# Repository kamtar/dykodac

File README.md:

# dykodac
Prototype of USB DAC using <b>CS4398</b>, AD712J and TPA6120A2 as a headphone amplifier. MCU - ATSAMD51<br>
Designed with 15V/1A transformer in mind, simple and linear power supply.

[Schematics in pdf](./schematics/DykoDAC.pdf)

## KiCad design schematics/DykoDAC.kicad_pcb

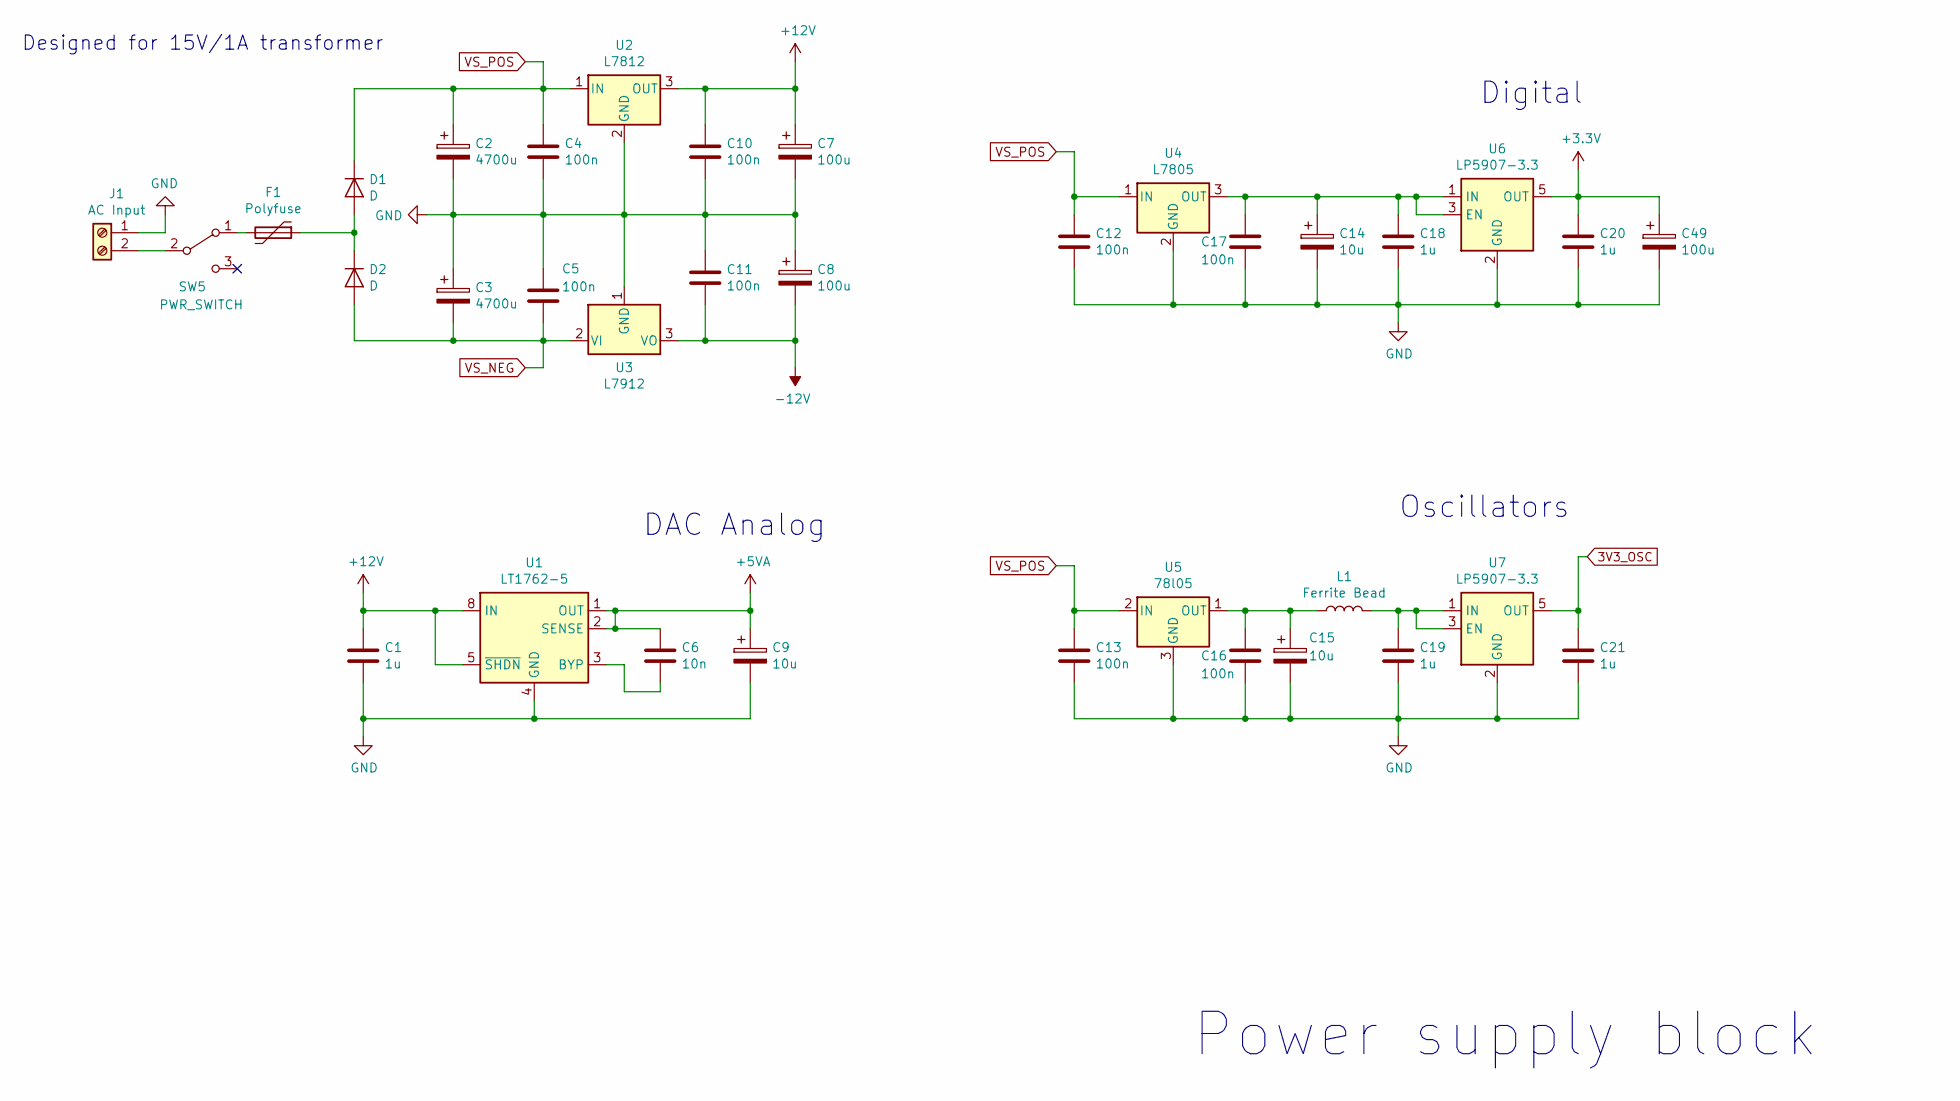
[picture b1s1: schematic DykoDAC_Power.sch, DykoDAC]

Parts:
C1, C18, C19, C20, C21: 1u; C_0603
C2, C3: 4700u; CP_Radial_D16.0mm_P7.50mm_Hor
C4, C5, C10, C11, C12, C13, C16, C17: 100n; C_0603
C6: 10n; C_0603
C7: 100u; CP_EIA-7343-31_Kemet-D; Part TAJD107K016SNJ
C8, C49: 100u; CP_EIA-7343-31_Kemet-D
C9: 10u; CP_EIA-3216-18_Kemet-A; Part T491A106K016AT
C14, C15: 10u; CP_EIA-3216-18_Kemet-A
D1, D2: D; D_SMB
F1: Polyfuse; UNIFuse_SMD2920
J1: AC Input; TerminalBlock_Altech_AK300-2_P5.00mm
L1: Ferrite Bead; C_0603
SW5: PWR_SWITCH; SW_Push_1P2T_Vertical_E-Switch_800UDP8P1A1M6
U1: LT1762-5; MSOP-8_3x3mm_Pitch0.65mm
U2: L7812; TO-263-2
U3: L7912; TO-263-2
U4: L7805; TO-263-2
U5: 78l05; SOT-23
U6, U7: LP5907-3.3; SOT-23-5

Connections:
3V3_OSC: C21.1, U7.5 (OUT); also elsewhere on the board
+5VA: C6.1, C9.1, U1.1 (OUT), U1.2 (SENSE); also elsewhere on the board
+12V: C1.1, C7.1, C10.1, U1.5 (~SHDN), U1.8 (IN), U2.3 (OUT); also elsewhere on the board
-12V: C8.2, C11.2, U3.3 (VO); also elsewhere on the board
GND: C1.2, C2.2, C3.1, C4.2, C5.1, C7.2, C8.1, C9.2, C10.2, C11.1, C12.2, C13.2, C14.2, C15.2, C16.2, C17.2, C18.2, C19.2, C20.2, C21.2, C49.2, J1.1, U1.4 (GND), U2.2 (GND), U3.1 (GND), U4.2 (GND), U5.3 (GND), U6.2 (GND), U7.2 (GND); also elsewhere on the board
unnamed: C6.2, U1.3 (BYP)
unnamed: C14.1, C17.1, C18.1, U4.3 (OUT), U6.1 (IN), U6.3 (EN)
unnamed: C15.1, C16.1, L1.1, U5.1 (OUT)
unnamed: C19.1, L1.2, U7.1 (IN), U7.3 (EN)
unnamed: D1.2 (A), D2.1 (K), F1.1
unnamed: F1.2, SW5.1 (A)
unnamed: J1.2, SW5.2 (B)
VS_NEG: C3.2, C5.2, D2.2 (A), U3.2 (VI)
VS_POS: C2.1, C4.1, C12.1, C13.1, D1.1 (K), U2.1 (IN), U4.1 (IN), U5.2 (IN)

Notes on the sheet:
Digital
DAC Analog
Power supply block
Oscillators
Designed for 15V/1A transformer

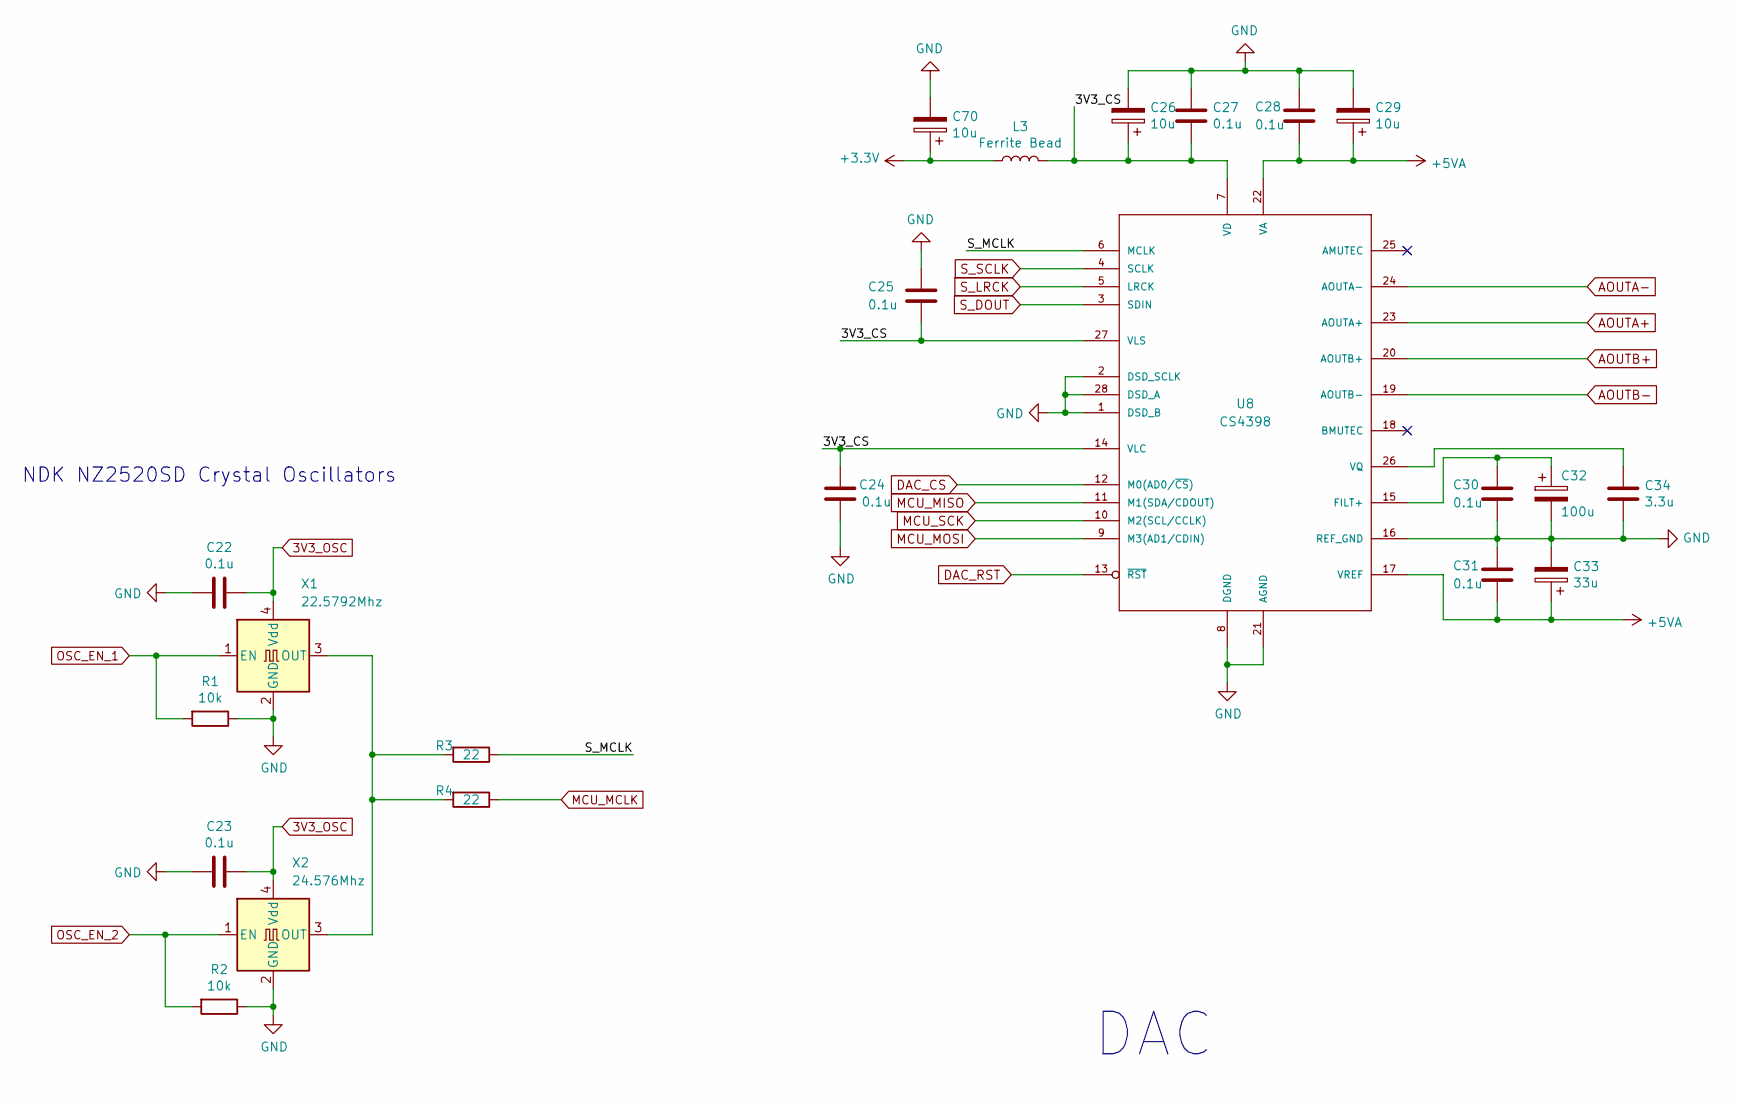
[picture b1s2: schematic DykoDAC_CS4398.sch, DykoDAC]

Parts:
C22, C23, C24, C25, C27, C28, C30, C31: 0.1u; C_0603
C26, C29, C70: 10u; CP_EIA-3216-18_Kemet-A
C32: 100u; CP_EIA-7343-31_Kemet-D; Part TAJD107K016SNJ
C33: 33u; CP_EIA-3216-18_Kemet-A
C34: 3.3u; C_0805
L3: Ferrite Bead; C_0603_1608Metric
R1, R2: 10k; R_0603
R3, R4: 22; R_0603
U8: CS4398; TSSOP-28_4.4x9.7mm_Pitch0.65mm
X1: 22.5792Mhz; Oscillator_SMD_SeikoEpson_SG210-4pin_2.5x2.0mm_HandSoldering; Part NDK NZ2520SD
X2: 24.576Mhz; Oscillator_SMD_SeikoEpson_SG210-4pin_2.5x2.0mm_HandSoldering; Part NDK NZ2520SD

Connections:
3V3_OSC: C22.1, C23.1, X1.4 (Vdd), X2.4 (Vdd); also elsewhere on the board
+5VA: C28.2, C29.1, C31.2, C33.1, U8.17 (VREF), U8.22 (VA); also elsewhere on the board
/DykoDAC_CS4398/3V3_CS: C24.1, C25.1, C26.1, C27.1, L3.2, U8.7 (VD), U8.14 (VLC), U8.27 (VLS)
/DykoDAC_CS4398/S_MCLK: R3.1, U8.6 (MCLK)
AOUTA+: U8.23 (AOUTA+); also elsewhere on the board
AOUTA-: U8.24 (AOUTA-); also elsewhere on the board
AOUTB+: U8.20 (AOUTB+); also elsewhere on the board
AOUTB-: U8.19 (AOUTB-); also elsewhere on the board
DAC_CS: U8.12 (M0(AD0/~CS~)); also elsewhere on the board
DAC_RST: U8.13 (~RST); also elsewhere on the board
GND: C22.2, C23.2, C24.2, C25.2, C26.2, C27.2, C28.1, C29.2, C30.2, C31.1, C32.2, C33.2, C34.2, C70.2, R1.1, R2.1, U8.1 (DSD_B), U8.2 (DSD_SCLK), U8.8 (DGND), U8.16 (REF_GND), U8.21 (AGND), U8.28 (DSD_A), X1.2 (GND), X2.2 (GND); also elsewhere on the board
MCU_MCLK: R4.1; also elsewhere on the board
MCU_MISO: U8.11 (M1(SDA/CDOUT)); also elsewhere on the board
MCU_MOSI: U8.9 (M3(AD1/CDIN)); also elsewhere on the board
MCU_SCK: U8.10 (M2(SCL/CCLK)); also elsewhere on the board
unnamed: C30.1, C32.1, U8.15 (FILT+)
unnamed: C34.1, U8.26 (VQ)
unnamed: R3.2, R4.2, X1.3 (OUT), X2.3 (OUT)
OSC_EN_1: R1.2, X1.1 (EN); also elsewhere on the board
OSC_EN_2: R2.2, X2.1 (EN); also elsewhere on the board
S_DOUT: U8.3 (SDIN); also elsewhere on the board
S_LRCK: U8.5 (LRCK); also elsewhere on the board
S_SCLK: U8.4 (SCLK); also elsewhere on the board

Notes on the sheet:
DAC
NDK NZ2520SD Crystal Oscillators

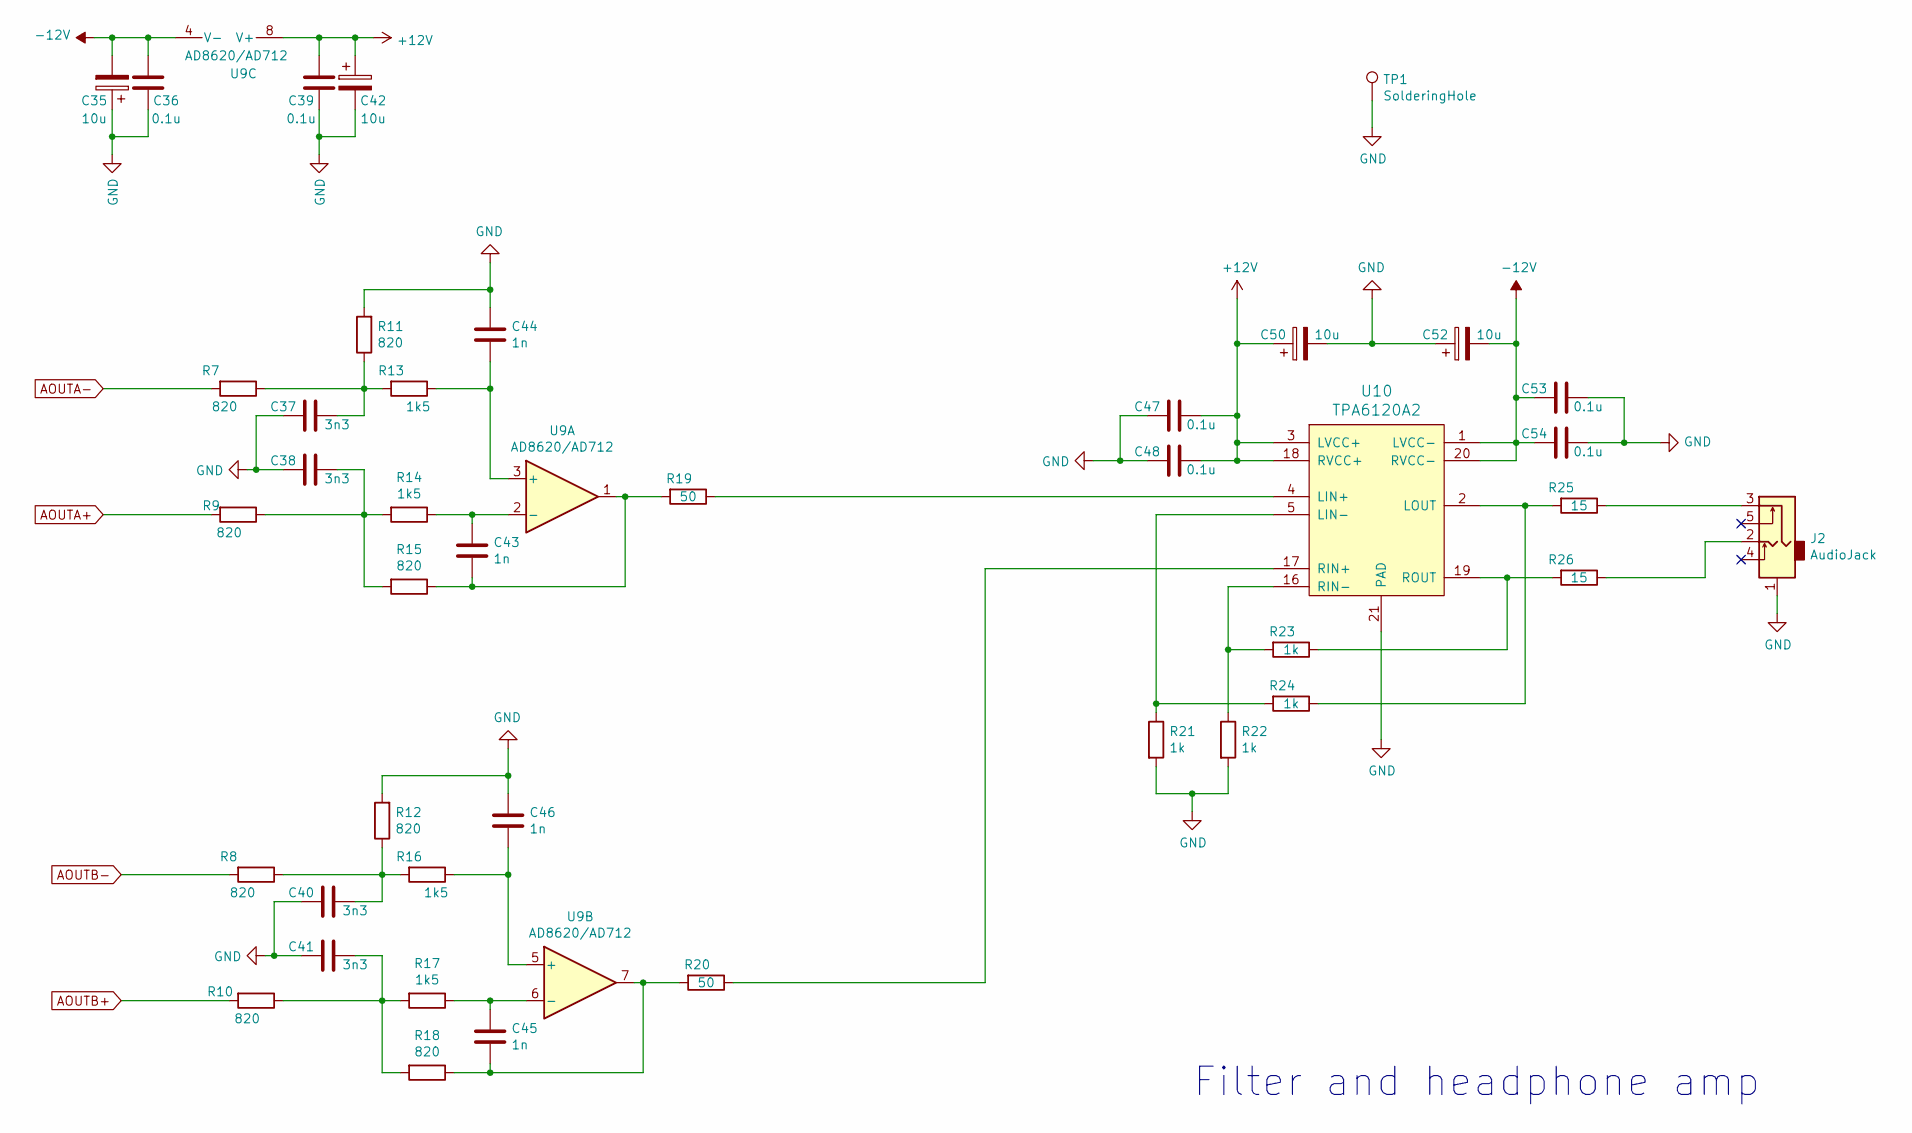
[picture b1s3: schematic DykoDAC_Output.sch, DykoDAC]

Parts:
C35, C42, C50, C52: 10u; CP_EIA-3216-18_Kemet-A
C36, C39, C47, C48, C53, C54: 0.1u; C_0603
C37, C38, C40, C41: 3n3; C_0603
C43, C44, C45, C46: 1n; C_0603
J2: AudioJack; StereoJack_3.5mm_Lumberg
R7, R8, R9, R10, R11, R12, R15, R18: 820; R_0603
R13, R14, R16, R17: 1k5; R_0603
R19, R20: 50; R_0603
R21, R22, R23, R24: 1k; R_0603
R25, R26: 15; R_0603
TP1: SolderingHole; TestPoint_Plated_Hole_D2.0mm
U9: AD8620/AD712; SOIC-8_3.9x4.9mm_Pitch1.27mm
U10: TPA6120A2; SOIC-20W_ThermalPad

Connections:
+12V: C39.2, C42.1, C47.1, C48.1, C50.1, U9.8 (V+), U10.3 (LVCC+), U10.18 (RVCC+); also elsewhere on the board
-12V: C35.2, C36.2, C52.2, C53.2, C54.2, U9.4 (V-), U10.1 (LVCC-), U10.20 (RVCC-); also elsewhere on the board
AOUTA+: R9.2; also elsewhere on the board
AOUTA-: R7.2; also elsewhere on the board
AOUTB+: R10.2; also elsewhere on the board
AOUTB-: R8.2; also elsewhere on the board
GND: C35.1, C36.1, C37.2, C38.2, C39.1, C40.2, C41.2, C42.2, C44.1, C46.1, C47.2, C48.2, C50.2, C52.1, C53.1, C54.1, J2.1, R11.2, R12.2, R21.2, R22.2, TP1.1, U10.21 (PAD); also elsewhere on the board
unnamed: C37.1, R7.1, R11.1, R13.2
unnamed: C38.1, R9.1, R14.2, R15.2
unnamed: C40.1, R8.1, R12.1, R16.2
unnamed: C41.1, R10.1, R17.2, R18.2
unnamed: C43.1, R14.1, U9.2 (-)
unnamed: C43.2, R15.1, R19.2, U9.1
unnamed: C44.2, R13.1, U9.3 (+)
unnamed: C45.1, R17.1, U9.6 (-)
unnamed: C45.2, R18.1, R20.2, U9.7
unnamed: C46.2, R16.1, U9.5 (+)
unnamed: J2.2, R26.1
unnamed: J2.3, R25.1
unnamed: R19.1, U10.4 (LIN+)
unnamed: R20.1, U10.17 (RIN+)
unnamed: R21.1, R24.2, U10.5 (LIN-)
unnamed: R22.1, R23.2, U10.16 (RIN-)
unnamed: R23.1, R26.2, U10.19 (ROUT)
unnamed: R24.1, R25.2, U10.2 (LOUT)

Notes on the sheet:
Filter and headphone amp

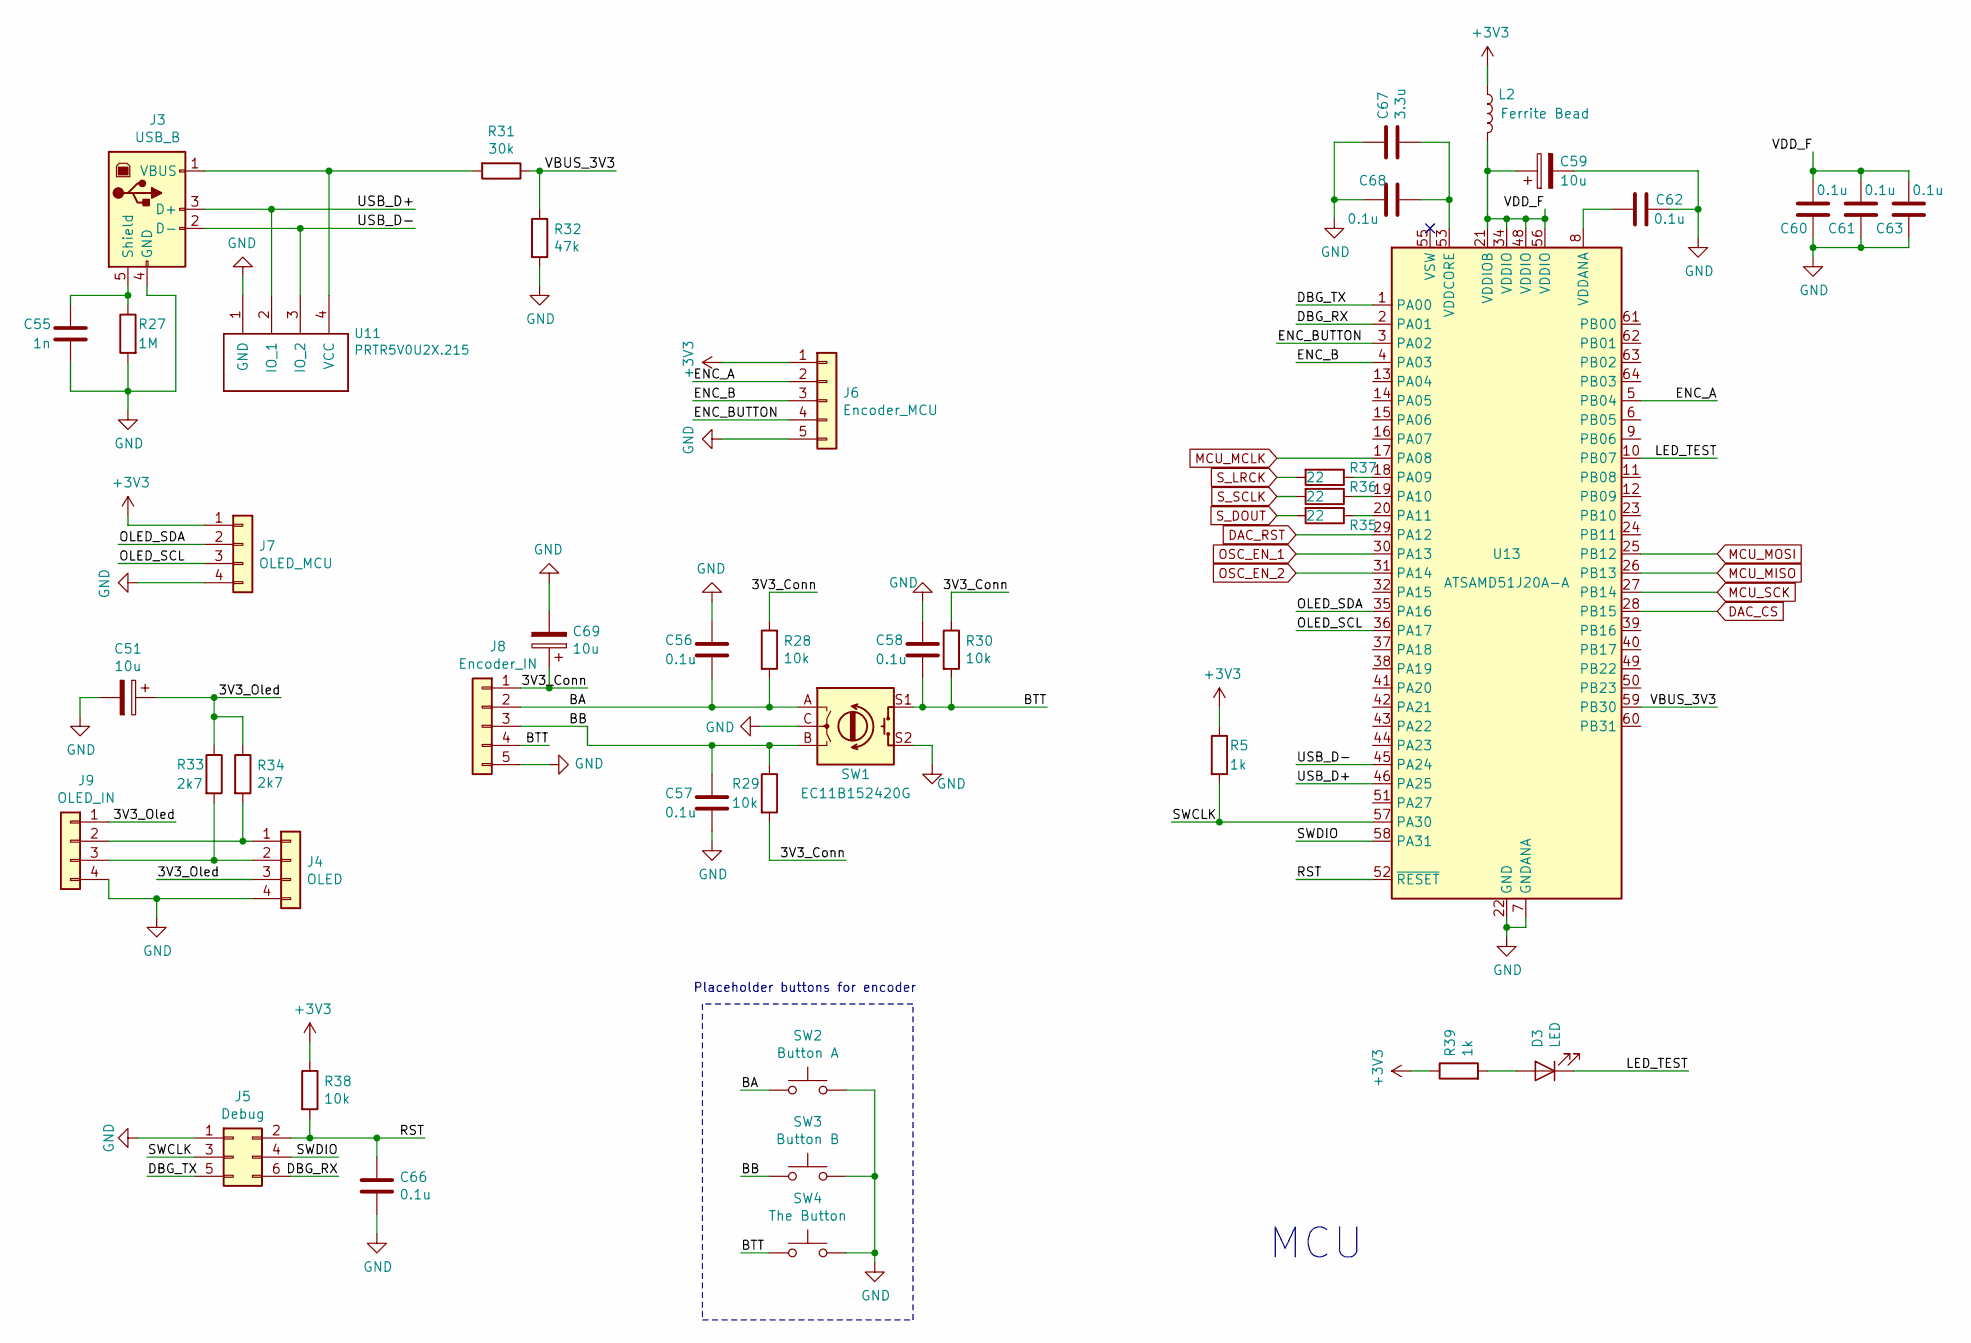
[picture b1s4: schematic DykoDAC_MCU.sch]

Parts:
C51, C59, C69: 10u; CP_EIA-3216-18_Kemet-A
C55: 1n; C_0603
C56, C57, C58, C60, C61, C62, C63, C66, C68: 0.1u; C_0603
C67: 3.3u; C_0805
D3: LED; LED_0603_HandSoldering
J3: USB_B
J4: OLED; Pin_Header_Straight_1x04_Pitch2.54mm
J5: Debug; Pin_Header_Straight_2x03_Pitch2.54mm
J6: Encoder_MCU; Pin_Header_Straight_1x05_Pitch2.00mm
J7: OLED_MCU; Pin_Header_Straight_1x04_Pitch2.00mm
J8: Encoder_IN; Pin_Header_Straight_1x05_Pitch2.00mm
J9: OLED_IN; Pin_Header_Straight_1x04_Pitch2.00mm
L2: Ferrite Bead; C_0603
R5, R39: 1k; R_0603
R27: 1M; R_0603
R28, R29, R30, R38: 10k; R_0603
R31: 30k; R_0603
R32: 47k; R_0603
R33, R34: 2k7; R_0603
R35, R36, R37: 22; R_0603
SW1: EC11B152420G; Potentiometer_Alps_RK097_Dual_Horizontal
SW2: Button A; SW_Tactile_SPST_Angled_PTS645Vx58-2LFS
SW3: Button B; SW_Tactile_SPST_Angled_PTS645Vx58-2LFS
SW4: The Button; SW_Tactile_SPST_Angled_PTS645Vx58-2LFS
U11: PRTR5V0U2X.215; SOT-143
U13: ATSAMD51J20A-A; LQFP-64_10x10mm_Pitch0.5mm

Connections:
/DykoDAC_MCU/3V3_Conn: C69.1, J8.1, R28.1, R29.2, R30.1
/DykoDAC_MCU/3V3_Oled: C51.1, J4.3, J9.1, R33.1, R34.1
/DykoDAC_MCU/BA: C56.2, J8.2, R28.2, SW1.A, SW2.1
/DykoDAC_MCU/BB: C57.1, J8.3, R29.1, SW1.B, SW3.1
/DykoDAC_MCU/BTT: C58.2, J8.4, R30.2, SW1.S1, SW4.1
/DykoDAC_MCU/DBG_RX: J5.6, U13.2 (PA01)
/DykoDAC_MCU/DBG_TX: J5.5, U13.1 (PA00)
/DykoDAC_MCU/ENC_A: J6.2, U13.5 (PB04)
/DykoDAC_MCU/ENC_B: J6.3, U13.4 (PA03)
/DykoDAC_MCU/ENC_BUTTON: J6.4, U13.3 (PA02)
/DykoDAC_MCU/LED_TEST: D3.1 (K), U13.10 (PB07)
/DykoDAC_MCU/OLED_SCL: J7.3, U13.36 (PA17)
/DykoDAC_MCU/OLED_SDA: J7.2, U13.35 (PA16)
/DykoDAC_MCU/RST: C66.1, J5.2, R38.2, U13.52 (~RESET)
/DykoDAC_MCU/SWCLK: J5.3, R5.2, U13.57 (PA30)
/DykoDAC_MCU/SWDIO: J5.4, U13.58 (PA31)
/DykoDAC_MCU/USB_D+: J3.3 (D+), U11.2 (IO_1), U13.46 (PA25)
/DykoDAC_MCU/USB_D-: J3.2 (D-), U11.3 (IO_2), U13.45 (PA24)
/DykoDAC_MCU/VBUS_3V3: R31.1, R32.1, U13.59 (PB30)
/DykoDAC_MCU/VDD_F: C59.1, C60.2, C61.2, C63.2, L2.2, U13.21 (VDDIOB), U13.34 (VDDIO), U13.48 (VDDIO), U13.56 (VDDIO)
DAC_CS: U13.28 (PB15); also elsewhere on the board
DAC_RST: U13.29 (PA12); also elsewhere on the board
GND: C51.2, C55.2, C56.1, C57.2, C58.1, C59.2, C60.1, C61.1, C62.1, C63.1, C66.2, C67.1, C68.2, C69.2, J3.4 (GND), J4.4, J5.1, J6.5, J7.4, J8.5, J9.4, R27.2, R32.2, SW1.C, SW1.S2, SW2.2, SW3.2, SW4.2, U11.1 (GND), U13.7 (GNDANA), U13.22 (GND), U13.33 (GND), U13.47 (GND), U13.54 (GND); also elsewhere on the board
MCU_MCLK: U13.17 (PA08); also elsewhere on the board
MCU_MISO: U13.26 (PB13); also elsewhere on the board
MCU_MOSI: U13.25 (PB12); also elsewhere on the board
MCU_SCK: U13.27 (PB14); also elsewhere on the board
unnamed: C55.1, J3.5 (Shield), R27.1
unnamed: C62.2, U13.8 (VDDANA)
unnamed: C67.2, C68.1, U13.53 (VDDCORE)
unnamed: D3.2 (A), R39.2
unnamed: J3.1 (VBUS), R31.2, U11.4 (VCC)
unnamed: J4.1, J9.2, R34.2
unnamed: J4.2, J9.3, R33.2
unnamed: R35.1, U13.20 (PA11)
unnamed: R36.1, U13.19 (PA10)
unnamed: R37.1, U13.18 (PA09)
OSC_EN_1: U13.30 (PA13); also elsewhere on the board
OSC_EN_2: U13.31 (PA14); also elsewhere on the board
S_DOUT: R35.2; also elsewhere on the board
S_LRCK: R37.2; also elsewhere on the board
S_SCLK: R36.2; also elsewhere on the board

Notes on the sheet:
MCU
Placeholder buttons for encoder

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
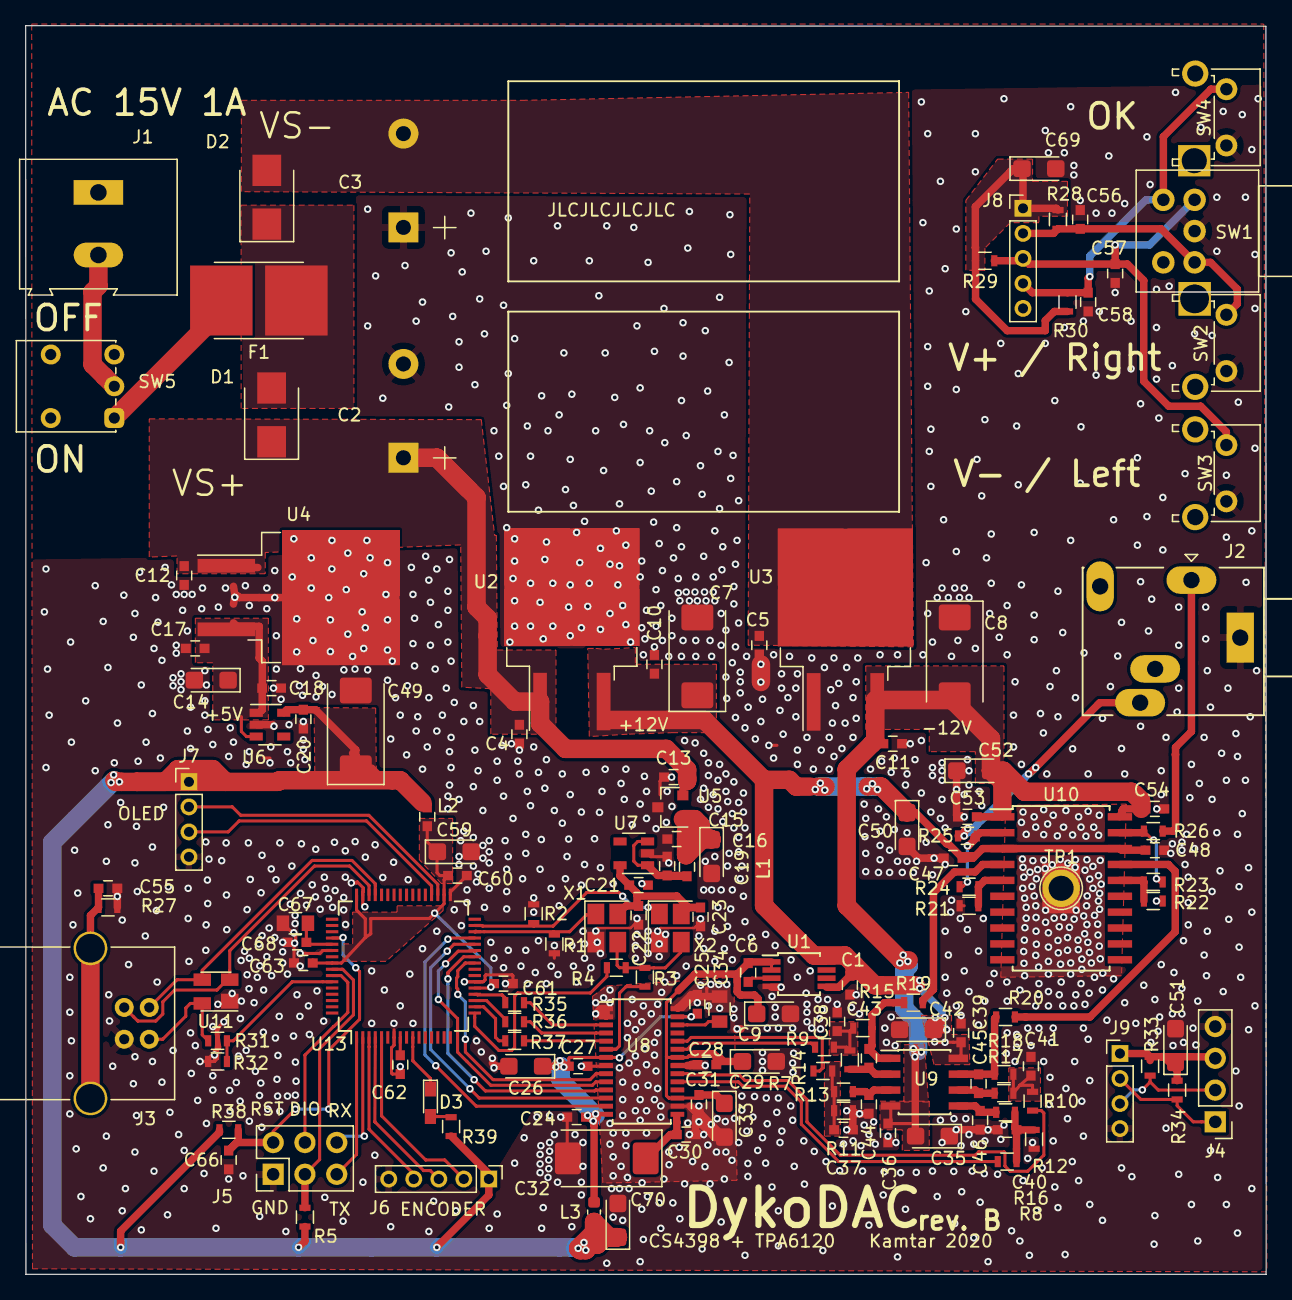
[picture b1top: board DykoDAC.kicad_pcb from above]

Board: 2 copper layers, 99.2 x 99.8 mm, 142 parts (0 on the bottom side), 83 nets.

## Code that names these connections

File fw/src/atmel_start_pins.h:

/*
 * Code generated from Atmel Start.
 *
 * This file will be overwritten when reconfiguring your Atmel Start project.
 * Please copy examples or other code you want to keep to a separate file
 * to avoid losing it when reconfiguring.
 */
#ifndef ATMEL_START_PINS_H_INCLUDED
#define ATMEL_START_PINS_H_INCLUDED

#include <hal_gpio.h>

// SAMD51 has 14 pin functions

#define GPIO_PIN_FUNCTION_A 0
#define GPIO_PIN_FUNCTION_B 1
#define GPIO_PIN_FUNCTION_C 2
#define GPIO_PIN_FUNCTION_D 3
#define GPIO_PIN_FUNCTION_E 4
#define GPIO_PIN_FUNCTION_F 5
#define GPIO_PIN_FUNCTION_G 6
#define GPIO_PIN_FUNCTION_H 7
#define GPIO_PIN_FUNCTION_I 8
#define GPIO_PIN_FUNCTION_J 9
#define GPIO_PIN_FUNCTION_K 10
#define GPIO_PIN_FUNCTION_L 11
#define GPIO_PIN_FUNCTION_M 12
#define GPIO_PIN_FUNCTION_N 13

#define PA00 GPIO(GPIO_PORTA, 0)
#define PA01 GPIO(GPIO_PORTA, 1)
#define PA08 GPIO(GPIO_PORTA, 8)
#define PA09 GPIO(GPIO_PORTA, 9)
#define PA10 GPIO(GPIO_PORTA, 10)
#define PA11 GPIO(GPIO_PORTA, 11)
#define PA16 GPIO(GPIO_PORTA, 16)
#define PA17 GPIO(GPIO_PORTA, 17)
#define PA22 GPIO(GPIO_PORTA, 17)
#define PA23 GPIO(GPIO_PORTA, 23)
#define PA24 GPIO(GPIO_PORTA, 24)
#define PA25 GPIO(GPIO_PORTA, 25)
#define PB04 GPIO(GPIO_PORTB, 04)
#define PB11 GPIO(GPIO_PORTB, 11)
#define PB12 GPIO(GPIO_PORTB, 12)
#define PB13 GPIO(GPIO_PORTB, 13)
#define PB14 GPIO(GPIO_PORTB, 14)

#endif // ATMEL_START_PINS_H_INCLUDED

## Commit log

2019-06-16 init schematics commit
2019-06-19 mcu input and usb added, oscilators moved to DAC schematics
2019-06-20 changed filter values, and cap in osscilator power supply.
2019-06-24 finishing
2019-06-24 cache
2019-06-29 changed filter values started with PCB design
2019-06-29 pcb dev.
2019-06-30 changed usb protection IC
2019-08-10 lots of stuf ....
2020-02-22 no message
2020-02-23 opamp filter pcb
2020-02-23 pcb update
2020-03-01 pdf update
2020-03-05 libraries
2020-03-06 minor chages
2020-03-09 first revision finished
2020-03-09 fixed via
2020-03-09 switch
2020-03-11 fix gnd trace under oscillators
2020-03-11 new footprint
2020-03-11 lm317 fix
2020-03-12 updated fuse
2020-03-12 fuse footprint
2020-03-12 added vias
2020-03-12 ldo change
2020-03-12 PRODUCTION - REV A
2020-03-13 3D update & pdf update
2020-03-13 9V -> 12V symbol
2020-03-17 PRODUCTION - REV.B - rotated 5Vreg. fixed 78l05, fixed wrong polygon
2020-03-17 minor changes & pdf update
2020-03-17 cosmetic changes
2020-04-09 bare fw first commit
2020-04-13 first "working" prototype
2020-04-17 first so-so working audio stream
2020-04-19 16bit/44.1 final prototype
2020-05-07 new pdf and minor changes in schematics and fw
